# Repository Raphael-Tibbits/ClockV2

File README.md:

# ClockV2
Crystal oscilator clock project

This project aims to create a 1s/year accurate clock, this is done with an ovenated crystal oscilator. 

There are two versions of the hardware, one with a discrete XO, which can be trimmed; and the other with a TCXO module that cant be trimmed

The hardware is made to be IEEE1101.3 compliant form factor as a 3U x 160 deep eurocard that occoupies 4HP. Mechanical stuff like a front panel is still to come.

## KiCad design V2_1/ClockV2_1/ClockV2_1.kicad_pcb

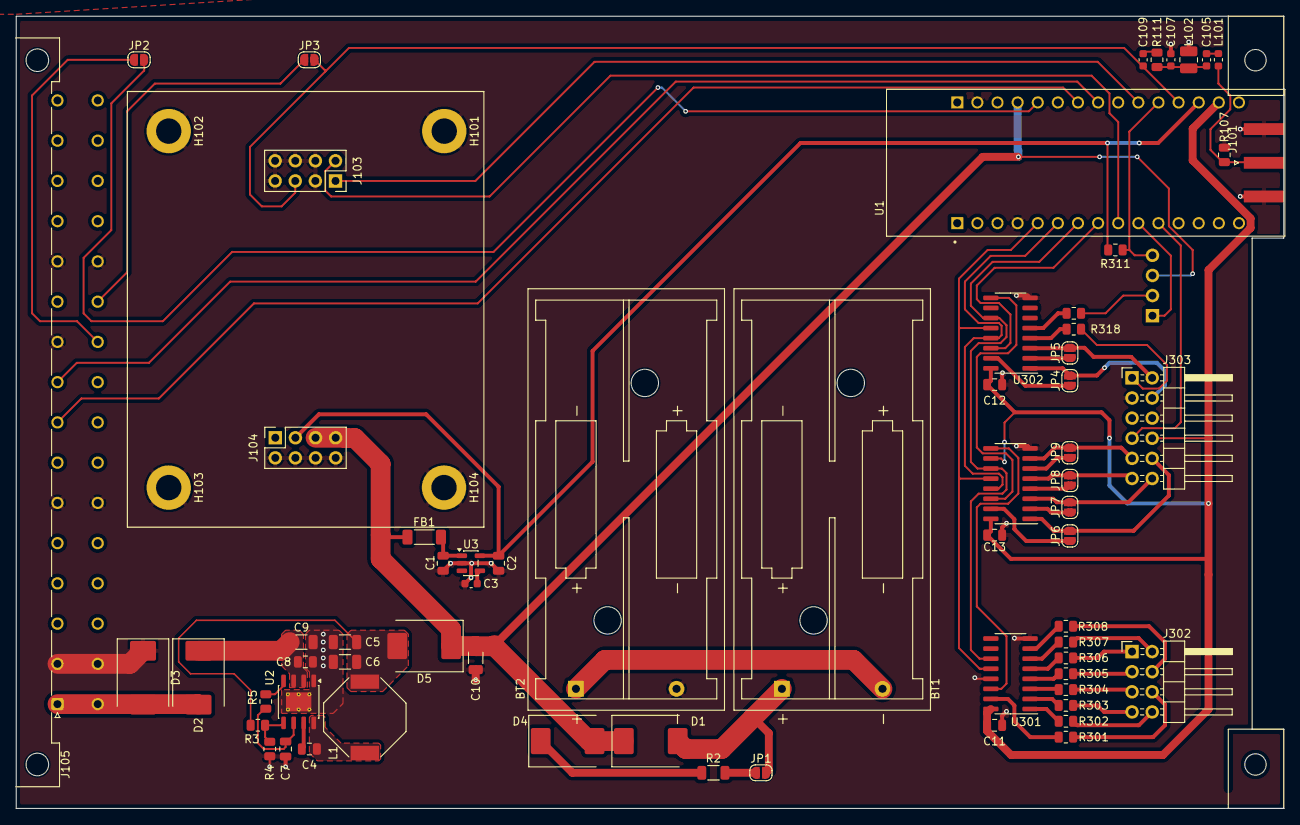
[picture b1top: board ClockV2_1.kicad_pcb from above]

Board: 2 copper layers, 160.0 x 100.0 mm, 70 parts (1 on the bottom side), 71 nets.

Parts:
BT1, BT2: 2.4V 2s NiMH; BatteryHolder_Keystone_2468_2xAAA
C1, C7, C11, C12, C13: 1u; C_0805_2012Metric
C2: 2.2u; C_0805_2012Metric
C3: 10n; C_0603_1608Metric
C4: 100n; C_0805_2012Metric
C5, C6, C10: 22u; C_1206_3216Metric
C8: 220n; C_0805_2012Metric
C9: 10u; C_1206_3216Metric
C105: 15p; C_0603_1608Metric
C107, C109: 150p; C_0603_1608Metric
D1, D2, D4, D5: B320; D_SMC
D3: 1.5SMCxxCA; D_SMC
FB1: FerriteBead; L_1806_4516Metric
H101, H102, H103, H104: MountingHole_Pad; MountingHole_3.2mm_M3_DIN965_Pad
J101: Conn_Coaxial; SMA_Amphenol_132289_EdgeMount
J103, J104: Conn_02x04_Odd_Even; PinSocket_2x04_P2.54mm_Vertical
J105: DIN41612_02x16_AC_EvenPins; DIN41612_C_2x16_Male_Horizontal_THT
J302: Conn_02x04_Odd_Even; PinHeader_2x04_P2.54mm_Horizontal
J303: Conn_02x06_Odd_Even; PinHeader_2x06_P2.54mm_Horizontal
JP1, JP2, JP3, JP4, JP5, JP6, JP7, JP8, JP9: SolderJumper_2_Open; SolderJumper-2_P1.3mm_Open_RoundedPad1.0x1.5mm
L1: 1.5u; L_Bourns-SRU1028_10.0x10.0mm
L101: 8.4u 2%; L_0603_1608Metric
L102: 620n 2%; L_1008_2520Metric
R2: 22R; R_1206_3216Metric
R3: 107k; R_0805_2012Metric
R4: 24.9k; R_0805_2012Metric
R5: 100k; R_0805_2012Metric
R107, R311: 1k; R_0805_2012Metric
R111: 330R; R_0805_2012Metric
R301, R302, R303, R304, R305, R306, R307, R308, R310, R318: 150; R_0805_2012Metric
U1: NUCLEO-L432KC; MODULE_NUCLEO-L432KC
U2: LMR33630CDDA; HTSOP-8-1EP_3.9x4.9mm_P1.27mm_EP2.4x3.2mm_ThermalVias
U3: LP2985-33DBVR; SOT-23-5
U301, U302, U303: 74HC595; SOIC-16_3.9x9.9mm_P1.27mm
j304: Conn_01x04; PinHeader_1x04_P2.54mm_Horizontal

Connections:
+3.3V: C11.1, C12.1, C13.1, J303.8, U1.CN4_14 (+3V3), U301.10 (~SRCLR), U301.16 (VCC), U302.10 (~SRCLR), U302.16 (VCC), U303.10 (~SRCLR), U303.16 (VCC)
+3.3VA: C2.1, J104.3, R311.1, U1.CN4_13 (AREF), U3.5 (VOUT)
+5V: C10.1, D1.1 (K), D4.2 (A), D5.1 (K), FB1.1, J104.5, J104.7, U1.CN4_4 (+5V), j304.3
+12P: D2.2 (A), D3.2 (A2), J105.a2, J105.c2
+12V: C8.2, C9.1, D2.1 (K), U2.2 (VIN), U2.3 (EN)
/1Hz: JP2.2 (B), U1.CN4_5 (PA2)
/16MHz sine: J101.1 (In), L101.2, R107.1
/Display driver and io/A1: J303.4, JP4.2 (B), U302.1 (QB)
/Display driver and io/A2: J303.2, JP5.2 (B), U302.3 (QD)
/Display driver and io/A5: J303.9, JP9.2 (B), U303.7 (QH)
/Display driver and io/A6: J303.11, JP8.2 (B), U303.5 (QF)
/Display driver and io/A7: J303.12, JP7.2 (B), U303.3 (QD)
/Display driver and io/A8: J303.10, JP6.2 (B), U303.1 (QB)
/Display driver and io/LED2: J303.1, R318.2
/Display driver and io/LED3: R310.1, j304.2
/Display driver and io/a: J302.2, R307.2
/Display driver and io/b: J302.1, R306.2
/Display driver and io/c: J302.5, R304.2
/Display driver and io/d: J302.8, R302.2
/Display driver and io/dp: J302.7, R303.2
/Display driver and io/e: J302.6, R301.2
/Display driver and io/f: J302.4, R308.2
/Display driver and io/g: J302.3, R305.2
/Heater_PWM: J103.2, U1.CN3_9 (PB1)
/OE: U1.CN3_6 (PB0), U302.13 (~OE), U303.13 (~OE)
/Ock: U1.CN3_5 (PA12), U301.12 (RCLK), U302.12 (RCLK), U303.12 (RCLK)
/SDA: U1.CN3_8 (PB6), U302.14 (SER)
/Thermistor: J103.1, U1.CN4_10 (PA3)
/Xtal: C109.1, J103.5, JP3.2 (B), U1.CN4_12 (PA0)
/sck: U1.CN3_7 (PB7), U301.11 (SRCLK), U302.11 (SRCLK), U303.11 (SRCLK)
Button: J303.7, U1.CN3_11 (PC15)
GND: BT2.2 (-), C1.2, C2.2, C3.2, C5.2, C6.2, C7.2, C8.1, C9.2, C10.2, C11.2, C12.2, C13.2, C107.2, D3.1 (A1), H101.1, H102.1, H103.1, H104.1, J101.2 (Ext), J103.3, J103.4, J103.6, J103.7, J103.8, J104.2, J104.4, J104.6, J104.8, J105.a4, J105.a12, J105.a20, J105.a24, J105.c4, J105.c12, J105.c24, J303.3, J303.6, L102.2, R4.2, R107.2, U1.CN3_4 (GND_CN3), U1.CN4_2 (GND_CN4), U2.1 (GND), U2.9 (GND), U3.2 (GND), U301.8 (GND), U301.13 (~OE), U302.8 (GND), U303.8 (GND)
I2C SCL: J105.a16, U1.CN4_7 (PA6)
I2C SDA: J105.a18, U1.CN4_8 (PA5)
LED: U1.CN3_10 (PC14), j304.1
unnamed: BT1.1 (+), D1.2 (A), JP1.2 (B)
unnamed: BT1.2 (-), BT2.1 (+)
unnamed: C105.1, C107.1, L102.1, R111.2
unnamed: C105.2, L101.1
unnamed: C109.2, R111.1
unnamed: D4.1 (K), R2.1
unnamed: C5.1, C6.1, D5.2 (A), L1.2, R3.1
unnamed: J105.c20, JP2.1 (A)
unnamed: J105.c22, JP3.1 (A)
unnamed: JP1.1 (A), R2.2
unnamed: JP4.1 (A), U302.15 (QA)
unnamed: JP5.1 (A), U302.2 (QC)
unnamed: JP6.1 (A), U303.15 (QA)
unnamed: JP7.1 (A), U303.2 (QC)
unnamed: JP8.1 (A), U303.4 (QE)
unnamed: JP9.1 (A), U303.6 (QG)
unnamed: C4.1, U2.7 (BOOT)
unnamed: R3.2, R4.1, U2.5 (FB)
unnamed: R5.2, U2.4 (PG)
unnamed: C4.2, L1.1, U2.8 (SW)
unnamed: C7.1, R5.1, U2.6 (VCC)
unnamed: C3.1, U3.4 (BYP)
unnamed: C1.1, FB1.2, U3.1 (VIN), U3.3 (ON/~OFF)
unnamed: R301.1, U301.15 (QA)
unnamed: R302.1, U301.1 (QB)
unnamed: R303.1, U301.2 (QC)
unnamed: R304.1, U301.3 (QD)
unnamed: R305.1, U301.4 (QE)
unnamed: R306.1, U301.5 (QF)
unnamed: R307.1, U301.6 (QG)
unnamed: R308.1, U301.7 (QH)
unnamed: U301.14 (SER), U303.9 (QH')
unnamed: R318.1, U302.4 (QE)
unnamed: R310.2, U302.5 (QF)
unnamed: U302.9 (QH'), U303.14 (SER)
light_sense: R311.2, U1.CN4_11 (PA1), j304.4

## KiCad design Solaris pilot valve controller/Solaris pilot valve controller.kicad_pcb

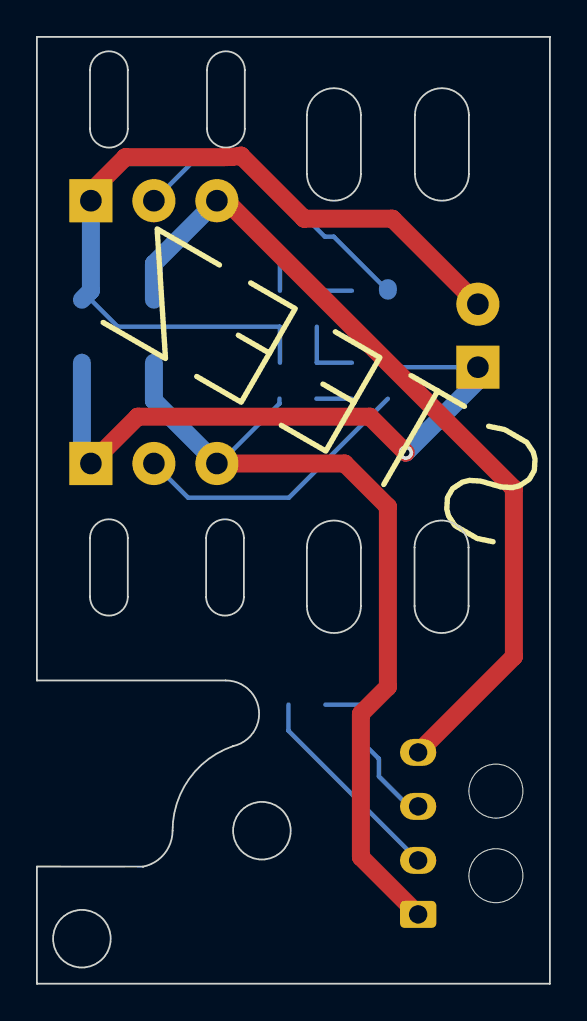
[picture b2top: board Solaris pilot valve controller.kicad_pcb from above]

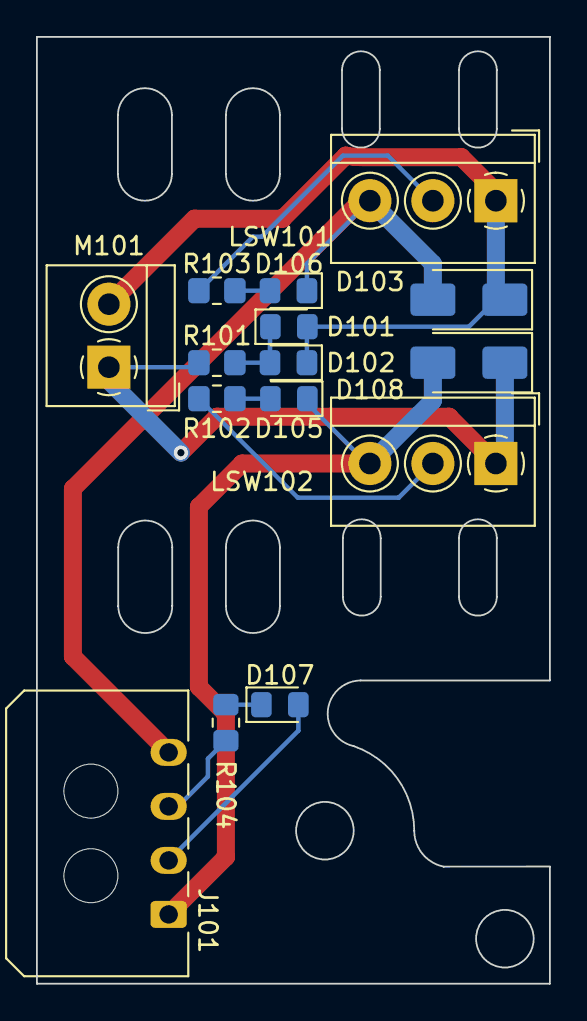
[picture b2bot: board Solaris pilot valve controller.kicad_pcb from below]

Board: 2 copper layers, 28.5 x 52.6 mm, 15 parts (15 on the bottom side), 12 nets.

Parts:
D101, D102, D105, D106, D107: LED; LED_0805_2012Metric_Pad1.15x1.40mm_HandSolder
D103, D108: M7; D_SMA
J101: 436500401; Molex_Micro-Fit_3.0_43650-0400_1x04_P3.00mm_Horizontal
LSW101, LSW102: SW_SPDT; TerminalBlock_4Ucon_1x03_P3.50mm_Horizontal
M101: Motor_DC_ALT; TerminalBlock_4Ucon_1x02_P3.50mm_Horizontal
R101, R102, R103, R104: 470R; R_0805_2012Metric_Pad1.20x1.40mm_HandSolder

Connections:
unnamed: D101.2 (A), D102.1 (K), D103.1 (K), LSW101.1 (COM), M101.2 (-)
unnamed: D101.1 (K), D102.2 (A), R101.1
unnamed: D103.2 (A), D106.1 (K), J101.4, LSW101.3 (NC)
unnamed: D105.2 (A), R102.1
unnamed: D105.1 (K), D108.2 (A), J101.1, LSW102.3 (NC)
unnamed: D106.2 (A), R103.1
unnamed: D107.2 (A), J101.2
unnamed: D107.1 (K), R104.2
unnamed: D108.1 (K), LSW102.1 (COM), M101.1 (+), R101.2
unnamed: J101.3, R104.1
unnamed: LSW101.2 (NO), R103.2
unnamed: LSW102.2 (NO), R102.2

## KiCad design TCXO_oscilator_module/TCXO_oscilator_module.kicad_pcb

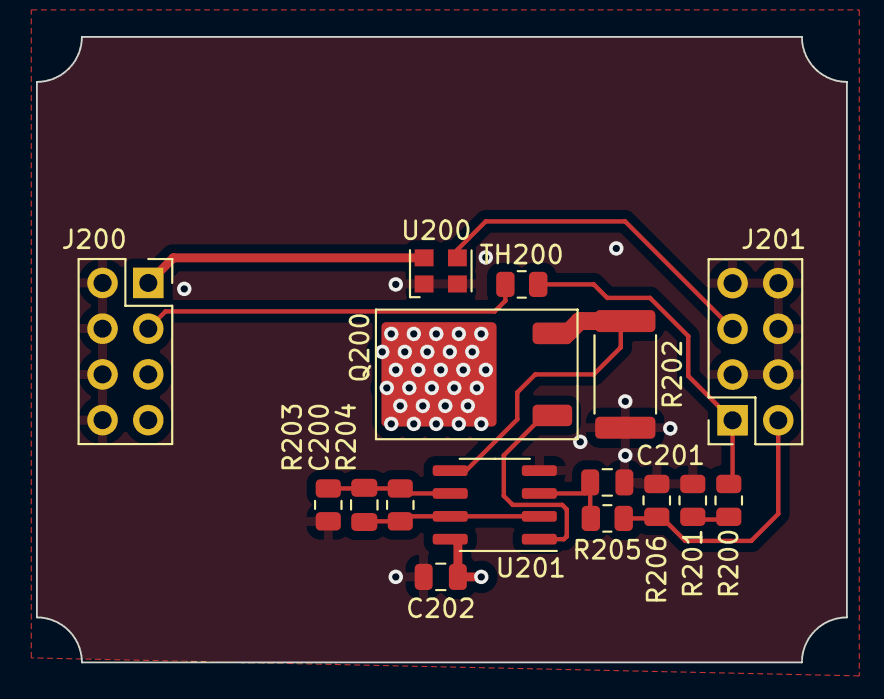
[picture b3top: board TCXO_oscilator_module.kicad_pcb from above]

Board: 4 copper layers, 45.0 x 34.8 mm, 16 parts (0 on the bottom side), 13 nets.

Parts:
C200, C201, C202: 1u; C_0805_2012Metric
J200, J201: Conn_02x04_Odd_Even; PinSocket_2x04_P2.54mm_Vertical
Q200: IRLR024N; TO-252-2
R200, R201, R203: 1k; R_0805_2012Metric
R202: 0.02R; R_2512_6332Metric
R204, R205, R206: 47k; R_0805_2012Metric
TH200: Thermistor_NTC; R_0805_2012Metric
U200: KC2520Z; Oscillator_SMD_Kyocera_KC2520Z-4Pin_2.5x2.0mm
U201: LMV358; SOIC-8_3.9x4.9mm_P1.27mm

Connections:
+2V5: J200.1, U200.4 (VCC)
+3.3VA: J200.3, TH200.1
+5V: C202.1, J200.5, J200.7, Q200.2 (D), U201.8 (V+)
/Heater_PWM: J201.2, R205.2, R206.2
/Thermistor: J201.1, R200.1, TH200.2
/XTAL1: J201.5, U200.3 (CLK)
GND: C201.2, C202.2, J200.2, J200.4, J200.6, J200.8, J201.3, J201.4, J201.6, J201.7, J201.8, R201.2, R202.2, R203.2, R206.1, U200.1 (INH), U200.2 (GND), U201.4 (V-)
unnamed: Q200.1 (G), U201.1
unnamed: Q200.3 (S), R202.1, U201.5 (+)
unnamed: R200.2, R201.1
unnamed: C201.1, R205.1, U201.3 (+)
unnamed: C200.2, R204.2, U201.2 (-), U201.7
unnamed: C200.1, R203.1, R204.1, U201.6 (-)

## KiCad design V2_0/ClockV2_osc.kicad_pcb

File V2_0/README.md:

# ClockV2
Crystal oscilator clock project

This project aims to create a 1s/year accurate clock, this is done with an ovenated crystal oscilator. 

There are two versions of the hardware, one with a discrete XO, which can be trimmed; and the other with a TCXO module that cant be trimmed

The hardware is made to be IEEE1101.3 compliant form factor as a 3U x 160 deep eurocard that occoupies 4HP. Mechanical stuff like a front panel is in progress

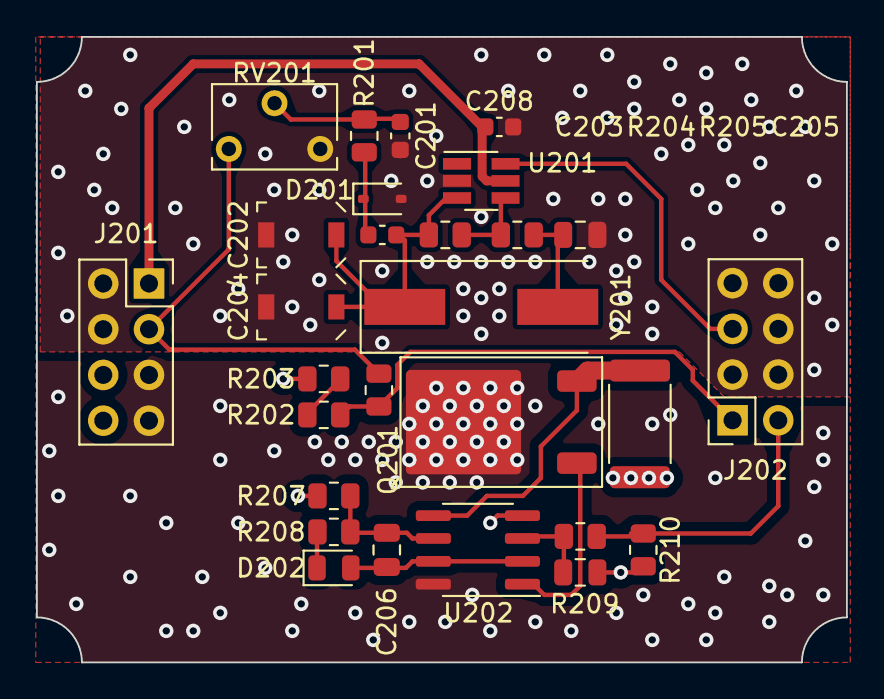
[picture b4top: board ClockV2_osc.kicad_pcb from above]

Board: 4 copper layers, 45.0 x 34.8 mm, 28 parts (0 on the bottom side), 19 nets.

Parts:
C201, C208: 10n; C_0603_1608Metric
C202: 0.1-2p; C_Trimmer_Voltronics_JZ
C203: 150p; C_0603_1608Metric
C204: 3-30p; C_Trimmer_Voltronics_JZ
C205: 22p C0G; C_0805_2012Metric
C206, C207: 1u; C_0805_2012Metric
D201: 1N4148WS; D_SOD-323
D202: LED; LED_0805_2012Metric
J201, J202: Conn_02x04_Odd_Even; PinSocket_2x04_P2.54mm_Vertical
Q201: IRLR024N; TO-252-2
R201, R208, R209, R210: 47k; R_0805_2012Metric
R202, R203, R207: 1k; R_0805_2012Metric
R204: 5M; R_0805_2012Metric
R205: 470R; R_0805_2012Metric
R206: 0.02R; R_2512_6332Metric
RV201: 10k; Potentiometer_Bourns_3266W_Vertical
TH201: Thermistor_NTC; R_0805_2012Metric
U201: 74LVC1GX04; SOT-23-6_Handsoldering
U202: LMV358; SOIC-8_3.9x4.9mm_P1.27mm
Y201: 16MHz; Crystal_SMD_HC49-SD

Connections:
+2V5: C208.1, J201.1, U201.5 (VCC)
+3.3VA: J201.3, RV201.1, TH201.1
+5V: J201.5, J201.7, Q201.2 (D), U202.8 (V+)
/16MHz clk: J202.5, U201.6 (Y)
/Heat: J202.2, R209.2, R210.2
/Temp: J202.1, R202.1, TH201.2
GND: C201.2, C202.2, C204.2, C205.2, C207.2, C208.2, D201.2 (A), J201.2, J201.4, J201.6, J201.8, J202.3, J202.4, J202.6, J202.7, J202.8, R203.2, R206.2, R207.2, R210.1, RV201.3, U201.2 (GND), U202.4 (V-)
unnamed: C201.1, R201.1, RV201.2
unnamed: C205.1, R205.2, Y201.2
unnamed: C203.1, D201.1 (K), R201.2
unnamed: C206.2, D202.2 (A), U202.2 (-), U202.7
unnamed: D202.1 (K), R208.2
unnamed: Q201.1 (G), U202.1
unnamed: Q201.3 (S), R206.1, U202.5 (+)
unnamed: R202.2, R203.1
unnamed: C202.1, C203.2, C204.1, R204.2, U201.3 (X1), Y201.1
unnamed: R204.1, R205.1, U201.4 (X2)
unnamed: C207.1, R209.1, U202.3 (+)
unnamed: C206.1, R207.1, R208.1, U202.6 (-)

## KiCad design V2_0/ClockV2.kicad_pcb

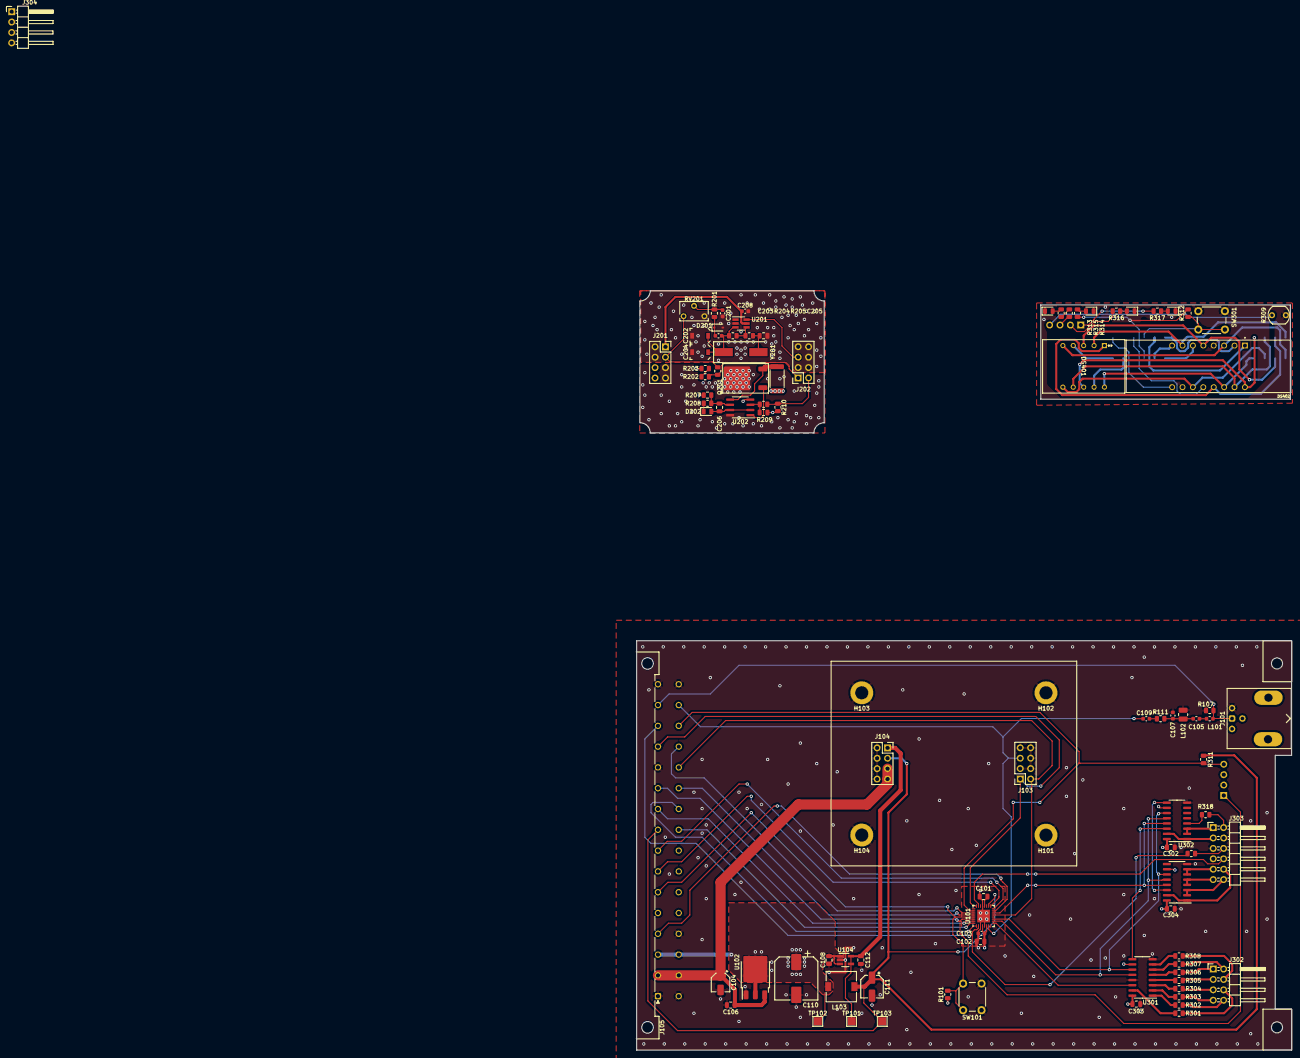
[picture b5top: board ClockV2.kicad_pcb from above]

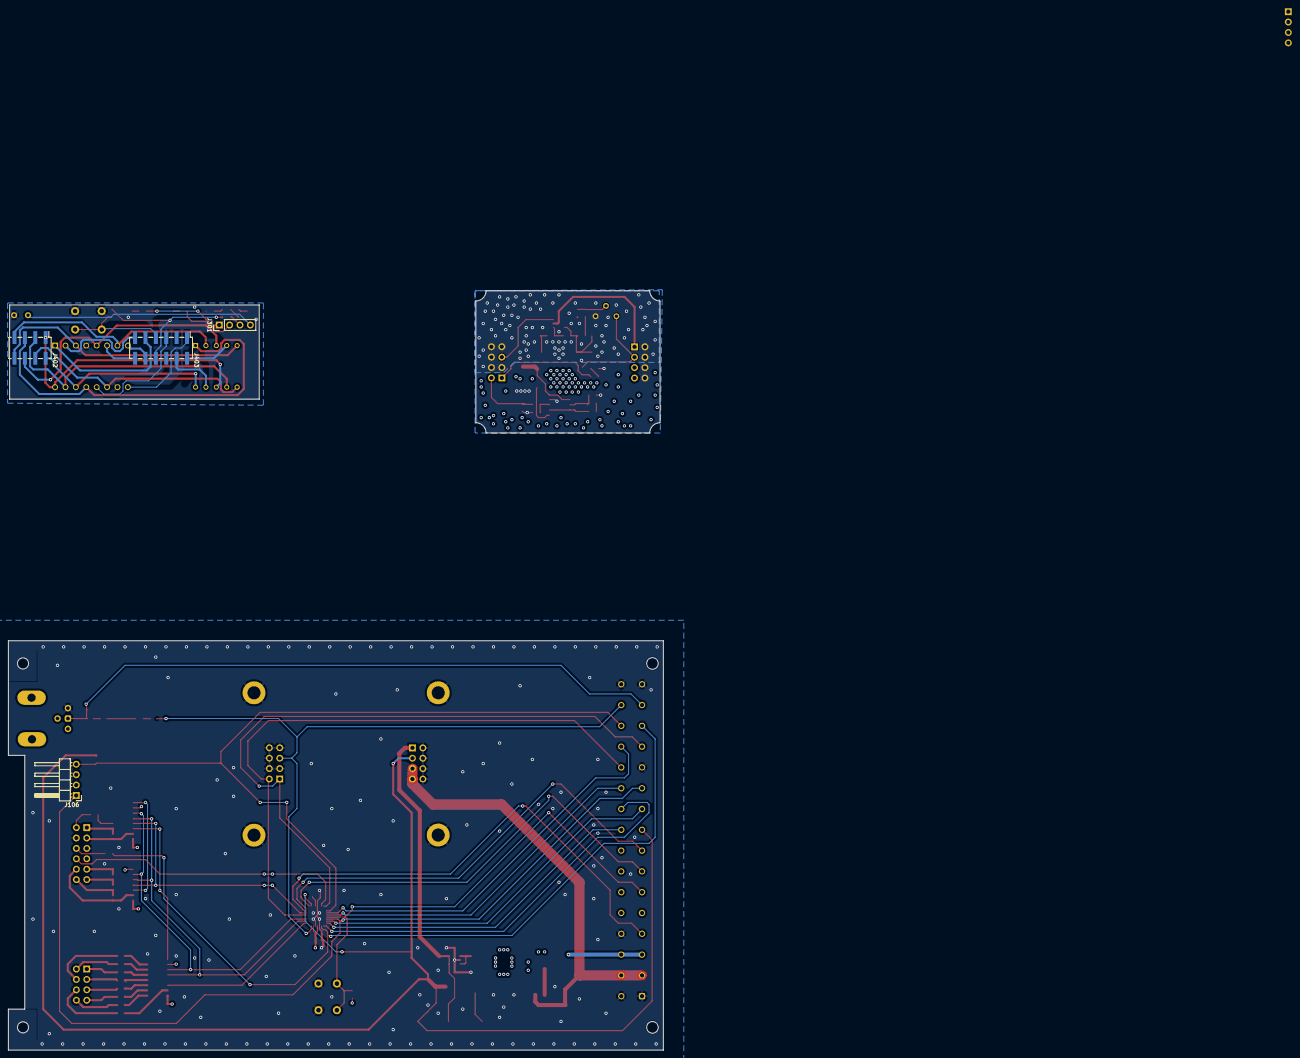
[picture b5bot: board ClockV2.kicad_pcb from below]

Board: 4 copper layers, 160.0 x 185.5 mm, 99 parts (4 on the bottom side), 74 nets.

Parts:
C101, C106, C108, C206, C207, C302, C303, C304: 1u; C_0805_2012Metric
C102: 100n; C_0805_2012Metric
C103, C201, C208: 10n; C_0603_1608Metric
C104: 4.7u; CP_Elec_4x3
C105: 15p; C_0603_1608Metric
C107, C109, C203: 150p; C_0603_1608Metric
C110: 220u; CP_Elec_10x10
C111: 47u; CP_Elec_5x3.9
C112: 2.2u; C_0805_2012Metric
C202: 0.1-2p; C_Trimmer_Voltronics_JZ
C204: 3-30p; C_Trimmer_Voltronics_JZ
C205: 22p C0G; C_0805_2012Metric
D201: 1N4148WS; D_SOD-323
D202: LED; LED_0805_2012Metric
D301, D302, D303: RED; LED_0805_2012Metric
D304: GRN; LED_0805_2012Metric
DS401: LTD-4608JR; LTD-4608JR_LTO
DS402: TDCR1060M; DISPLAY_TDCR1060M
H101, H102, H103, H104: MountingHole_Pad; MountingHole_3.2mm_M3_DIN965_Pad
J101: Conn_Coaxial; BNC_Amphenol_031-6575_Horizontal
J103, J104, J201, J202: Conn_02x04_Odd_Even; PinSocket_2x04_P2.54mm_Vertical
J105: DIN41612_02x16_AC_EvenPins; DIN41612_C_2x16_Male_Horizontal_THT
J106, J304: Conn_01x04; PinHeader_1x04_P2.54mm_Horizontal
J301: Conn_01x04; PinHeader_1x04_P2.54mm_Vertical
J302: Conn_02x04_Odd_Even; PinHeader_2x04_P2.54mm_Horizontal
J303: Conn_02x06_Odd_Even; PinHeader_2x06_P2.54mm_Horizontal
J402: Conn_02x04_Odd_Even; PinHeader_2x04_P2.54mm_Vertical_SMD
J403: Conn_02x06_Odd_Even; PinHeader_2x06_P2.54mm_Vertical_SMD
L101: 8.4u 2%; L_0603_1608Metric
L102: 620n 2%; L_1008_2520Metric
L103: 1m; L_7.3x7.3_H3.5
Q201: IRLR024N; TO-252-2
R101, R201, R208, R209, R210: 47k; R_0805_2012Metric
R107, R202, R203, R207, R311, R312: 1k; R_0805_2012Metric
R111, R313, R314, R315: 330R; R_0805_2012Metric
R204: 5M; R_0805_2012Metric
R205: 470R; R_0805_2012Metric
R206: 0.02R; R_2512_6332Metric
R301, R302, R303, R304, R305, R306, R307, R308, R310, R316, R317, R318: 150; R_0805_2012Metric
R309: LDR03; R_LDR_5.1x4.3mm_P3.4mm_Vertical
RV201: 10k; Potentiometer_Bourns_3266W_Vertical
SW101, SW301: SW_Push; SW_PUSH_6mm_H4.3mm
TH201: Thermistor_NTC; R_0805_2012Metric
TP101, TP102, TP103: TestPoint; TestPoint_Pad_2.0x2.0mm
U101: ATmega328P-M; QFN-32-1EP_5x5mm_P0.5mm_EP3.1x3.1mm
U102: LM1117DT-3.3; TO-252-3_TabPin2
U104: ADP7142ARDZ-2.5; SOT-23-5_HandSoldering
U201: 74LVC1GX04; SOT-23-6_Handsoldering
U202: LMV358; SOIC-8_3.9x4.9mm_P1.27mm
U301, U302, U303: 74HC595; SOIC-16_3.9x9.9mm_P1.27mm
Y201: 16MHz; Crystal_SMD_HC49-SD

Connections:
+2V5: C112.1, C208.1, J104.1, J106.2, J201.1, J301.2, J304.2, R316.2, TP101.1, U104.4 (SENSE/ADJ), U104.5 (VOUT), U201.5 (VCC)
+3.3V: C102.1, C103.1, C108.1, C110.1, C302.1, C303.1, C304.1, J105.a6, J105.c6, J303.7, J403.8, L103.1, R101.1, R312.1, R314.1, TP102.1, U101.4 (VCC), U101.6 (VCC), U102.2 (VO), U104.1 (VIN), U104.3 (EN), U301.10 (~SRCLR), U301.16 (VCC), U302.10 (~SRCLR), U302.16 (VCC), U303.10 (~SRCLR), U303.16 (VCC)
+3.3VA: C111.1, J104.3, J105.a18, J201.3, L103.2, R311.1, RV201.1, TH201.1, TP103.1, U101.18 (AVCC)
+5V: C104.1, C106.1, J104.5, J104.7, J105.a4, J105.c4, J106.3, J201.5, J201.7, J301.3, J304.3, Q201.2 (D), R315.1, U102.3 (VI), U202.8 (V+)
/1Hz: J105.a28, R310.2, U101.2 (PD4)
/7 seg Display/1PPS: DS402.12, J303.6, J403.5, R310.1
/7 seg Display/A1: DS401.9, J303.3, J403.4, U302.1 (QB), U302.15 (QA)
/7 seg Display/A2: DS401.4, J303.1, J403.2, U302.2 (QC), U302.3 (QD)
/7 seg Display/A5: DS402.1, J303.10, J403.9, U303.1 (QB), U303.15 (QA)
/7 seg Display/A6: DS402.2, J303.12, J403.11, U303.2 (QC), U303.3 (QD)
/7 seg Display/A7: DS402.6, J303.11, J403.12, U303.4 (QE), U303.5 (QF)
/7 seg Display/A8: DS402.8, J303.9, J403.10, U303.6 (QG), U303.7 (QH)
/7 seg Display/LED2: DS402.9, J303.2, J403.1, R318.2
/7 seg Display/ORClk: U101.10 (PD6), U301.12 (RCLK), U302.12 (RCLK), U303.12 (RCLK)
/7 seg Display/OutEn: U101.14 (PB2), U302.13 (~OE), U303.13 (~OE)
/7 seg Display/Sclk: U101.11 (PD7), U301.11 (SRCLK), U302.11 (SRCLK), U303.11 (SRCLK)
/7 seg Display/SerData: U101.9 (PD5), U301.14 (SER)
/7 seg Display/a: DS401.10, DS402.14, J302.2, J402.2, R307.2
/7 seg Display/b: DS401.8, DS402.16, J302.1, J402.1, R306.2
/7 seg Display/c: DS401.1, DS402.13, J302.5, J402.5, R304.2
/7 seg Display/d: DS401.5, DS402.3, J302.8, J402.8, R302.2
/7 seg Display/dp: DS401.2, DS402.7, J302.7, J402.7, R303.2
/7 seg Display/e: DS401.3, DS402.5, J302.6, J402.6, R301.2
/7 seg Display/f: DS401.6, DS402.11, J302.4, J402.4, R308.2
/7 seg Display/g: DS401.7, DS402.15, J302.3, J402.3, R305.2
/16MHz clk: C109.1, J103.5, J105.c30, J202.5, U101.7 (XTAL1/PB6), U201.6 (Y)
/16MHz sine: J101.1 (In), J105.a30, L101.2, R107.1
/AIO0: J105.c22, U101.28 (PC5)
/AIO1: J105.c26, U101.27 (PC4)
/DIO0: J105.a20, U101.31 (PD1)
/DIO1: J105.c18, U101.32 (PD2)
/DIO2: J105.c20, U101.1 (PD3)
/Heat: J103.2, J105.c24, J202.2, R209.2, R210.2, U101.13 (PB1)
/Temp: J103.1, J105.a26, J202.1, R202.1, TH201.2, U101.24 (PC1)
/miso: J105.a16, U101.16 (PB4)
/mosi: J105.a8, U101.15 (PB3)
/rst: J105.a12, R101.2, SW101.1, U101.29 (~RESET/PC6)
/sck: J105.a14, U101.17 (PB5)
Button: J303.8, J403.7, R312.2, SW301.1, U101.23 (PC0)
GND: C101.2, C102.2, C103.2, C104.2, C106.2, C107.2, C108.2, C110.2, C111.2, C112.2, C201.2, C202.2, C204.2, C205.2, C207.2, C208.2, C302.2, C303.2, C304.2, D201.2 (A), D301.1 (K), D302.1 (K), D303.1 (K), D304.1 (K), DS402.4, DS402.10, H101.1, H102.1, H103.1, H104.1, J101.2 (Ext), J103.3, J103.4, J103.6, J103.7, J103.8, J104.2, J104.4, J104.6, J104.8, J105.a2, J105.a24, J105.a32, J105.c2, J105.c8, J105.c32, J201.2, J201.4, J201.6, J201.8, J202.3, J202.4, J202.6, J202.7, J202.8, J303.4, J303.5, J403.3, J403.6, L102.2, R107.2, R203.2, R206.2, R207.2, R210.1, R309.2, RV201.3, SW101.2, SW301.2, U101.3 (GND), U101.5 (GND), U101.21 (GND), U101.33 (GND), U102.1 (GND), U104.2 (GND), U201.2 (GND), U202.4 (V-), U301.8 (GND), U301.13 (~OE), U302.8 (GND), U303.8 (GND)
LED: J105.a22, J106.1, J301.1, J304.1, R317.2, U101.30 (PD0)
unnamed: C105.1, C107.1, L102.1, R111.2
unnamed: C105.2, L101.1
unnamed: C109.2, R111.1
unnamed: C201.1, R201.1, RV201.2
unnamed: C205.1, R205.2, Y201.2
unnamed: C203.1, D201.1 (K), R201.2
unnamed: C206.2, D202.2 (A), U202.2 (-), U202.7
unnamed: D202.1 (K), R208.2
unnamed: D301.2 (A), R313.2
unnamed: D302.2 (A), R314.2
unnamed: D303.2 (A), R316.1
unnamed: D304.2 (A), R317.1
unnamed: Q201.1 (G), U202.1
unnamed: Q201.3 (S), R206.1, U202.5 (+)
unnamed: R202.2, R203.1
unnamed: R313.1, R315.2
unnamed: C101.1, U101.20 (AREF)
unnamed: C202.1, C203.2, C204.1, R204.2, U201.3 (X1), Y201.1
unnamed: R204.1, R205.1, U201.4 (X2)
unnamed: C207.1, R209.1, U202.3 (+)
unnamed: C206.1, R207.1, R208.1, U202.6 (-)
unnamed: R301.1, U301.15 (QA)
unnamed: R302.1, U301.1 (QB)
unnamed: R303.1, U301.2 (QC)
unnamed: R304.1, U301.3 (QD)
unnamed: R305.1, U301.4 (QE)
unnamed: R306.1, U301.5 (QF)
unnamed: R307.1, U301.6 (QG)
unnamed: U301.9 (QH'), U302.14 (SER)
unnamed: R308.1, U301.7 (QH)
unnamed: R318.1, U302.4 (QE)
unnamed: U302.9 (QH'), U303.14 (SER)
light_sense: J105.c28, J106.4, J301.4, J304.4, R309.1, R311.2, U101.26 (PC3)

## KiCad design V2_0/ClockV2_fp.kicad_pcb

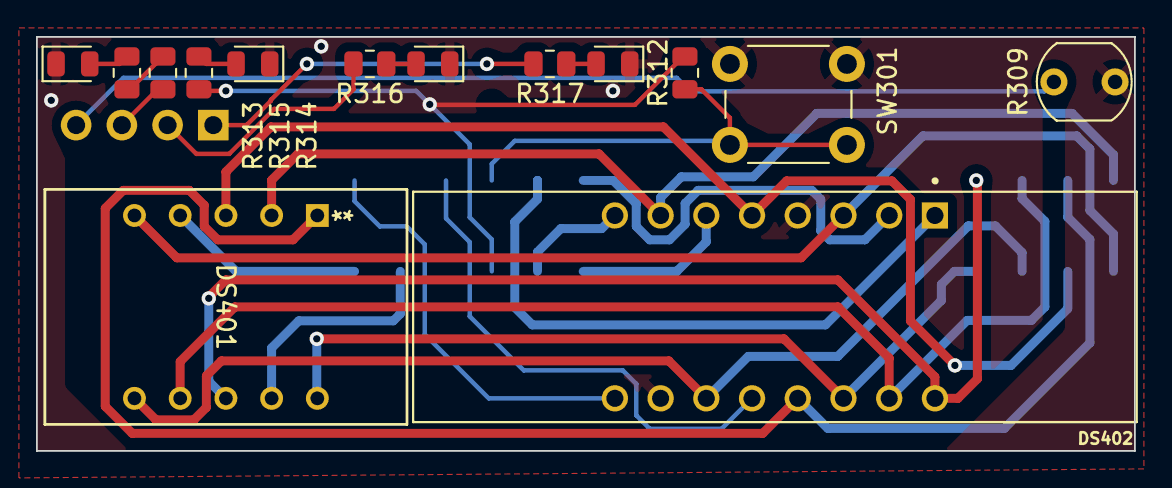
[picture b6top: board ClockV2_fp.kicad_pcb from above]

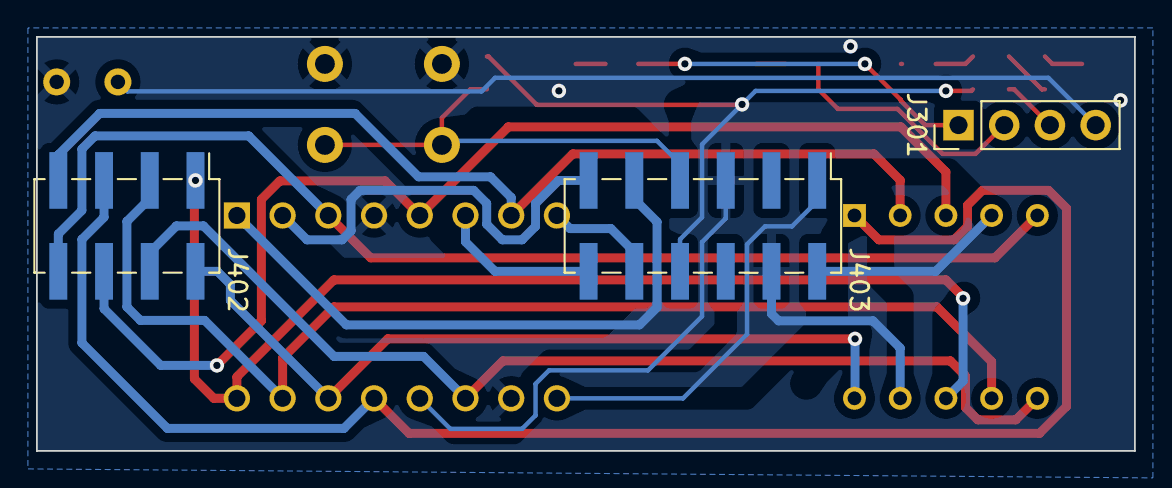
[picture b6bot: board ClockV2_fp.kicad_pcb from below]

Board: 4 copper layers, 61.0 x 23.0 mm, 17 parts (3 on the bottom side), 28 nets.

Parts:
D301, D302, D303: RED; LED_0805_2012Metric
D304: GRN; LED_0805_2012Metric
DS401: LTD-4608JR; LTD-4608JR_LTO
DS402: TDCR1060M; DISPLAY_TDCR1060M
J301: Conn_01x04; PinHeader_1x04_P2.54mm_Vertical
J402: Conn_02x04_Odd_Even; PinHeader_2x04_P2.54mm_Vertical_SMD
J403: Conn_02x06_Odd_Even; PinHeader_2x06_P2.54mm_Vertical_SMD
R309: LDR03; R_LDR_5.1x4.3mm_P3.4mm_Vertical
R312: 1k; R_0805_2012Metric
R313, R314, R315: 330R; R_0805_2012Metric
R316, R317: 150; R_0805_2012Metric
SW301: SW_Push; SW_PUSH_6mm_H4.3mm

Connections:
+2V5: J301.2, R316.2
+3.3V: J403.8, R312.1, R314.1
+5V: J301.3, R315.1
/7 seg Display/1PPS: DS402.12, J403.5
/7 seg Display/A1: DS401.9, J403.4
/7 seg Display/A2: DS401.4, J403.2
/7 seg Display/A5: DS402.1, J403.9
/7 seg Display/A6: DS402.2, J403.11
/7 seg Display/A7: DS402.6, J403.12
/7 seg Display/A8: DS402.8, J403.10
/7 seg Display/LED2: DS402.9, J403.1
/7 seg Display/a: DS401.10, DS402.14, J402.2
/7 seg Display/b: DS401.8, DS402.16, J402.1
/7 seg Display/c: DS401.1, DS402.13, J402.5
/7 seg Display/d: DS401.5, DS402.3, J402.8
/7 seg Display/dp: DS401.2, DS402.7, J402.7
/7 seg Display/e: DS401.3, DS402.5, J402.6
/7 seg Display/f: DS401.6, DS402.11, J402.4
/7 seg Display/g: DS401.7, DS402.15, J402.3
Button: J403.7, R312.2, SW301.1
GND: D301.1 (K), D302.1 (K), D303.1 (K), D304.1 (K), DS402.4, DS402.10, J403.3, J403.6, R309.2, SW301.2
LED: J301.1, R317.2
unnamed: D301.2 (A), R313.2
unnamed: D302.2 (A), R314.2
unnamed: D303.2 (A), R316.1
unnamed: D304.2 (A), R317.1
unnamed: R313.1, R315.2
light_sense: J301.4, R309.1

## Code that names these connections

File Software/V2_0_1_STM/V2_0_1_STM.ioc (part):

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Mcu.Name=STM32L432K(B-C)Ux
Mcu.Package=UFQFPN32
Mcu.UserName=STM32L432KCUx
PA0.GPIOParameters=GPIO_Label
PA0.GPIO_Label=HSE_16MHZ
PA0.Mode=HSE-External-Clock-Source-for-LittleOrca
PA0.Signal=RCC_CK_IN
PA1.GPIOParameters=GPIO_Label
PA1.GPIO_Label=LDR_sense
PA1.Signal=SharedAnalog_PA1
PA10.Mode=I2C
PA10.Signal=I2C1_SDA
PA2.Mode=Asynchronous
PA2.Signal=USART2_TX
PA3.Mode=Asynchronous
PA3.Signal=USART2_RX
PA4.GPIOParameters=GPIO_Label
PA4.GPIO_Label=Therm_sense
PA4.Signal=SharedAnalog_PA4
PA5.GPIOParameters=GPIO_Label
PA5.GPIO_Label=Display_SCK
PA5.Mode=TX_Only_Simplex_Unidirect_Master
PA5.Signal=SPI1_SCK
PA6.GPIOParameters=GPIO_Label
PA6.GPIO_Label=Display_RCK
PA6.Signal=GPIO_Output
PA7.GPIOParameters=GPIO_Label
PA7.GPIO_Label=Display_MOSI
PA7.Mode=TX_Only_Simplex_Unidirect_Master
PA7.Signal=SPI1_MOSI
PA9.Mode=I2C
PA9.Signal=I2C1_SCL
PB0.GPIOParameters=GPIO_Label
PB0.GPIO_Label=Display_PWM
PB0.Mode=PWM Generation2 CH2N
PB0.Signal=TIM1_CH2N
PB1.GPIOParameters=GPIO_Label
PB1.GPIO_Label=Heater_PWM
PB1.Mode=PWM Generation3 CH3N
PB1.Signal=TIM1_CH3N
PB3\ (JTDO-TRACESWO).Signal=GPIO_Output
RCC.HSE_VALUE=16000000
RCC.SYSCLKFreq_VALUE=64000000
RCC.SYSCLKSource=RCC_SYSCLKSOURCE_PLLCLK
board=custom

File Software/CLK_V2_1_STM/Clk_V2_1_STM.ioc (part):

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Mcu.Name=STM32L432K(B-C)Ux
Mcu.Package=UFQFPN32
Mcu.UserName=STM32L432KCUx
PA0.Mode=HSE-External-Clock-Source-for-LittleOrca
PA0.Signal=RCC_CK_IN
PA1.GPIOParameters=GPIO_Label
PA1.GPIO_Label=Light_sensor
PA1.Signal=ADCx_IN6
PA10.Mode=I2C
PA10.Signal=I2C1_SDA
PA11.GPIOParameters=GPIO_Label
PA11.GPIO_Label=DISP_OE
PA11.Signal=S_TIM1_CH4
PA12.GPIOParameters=GPIO_Label
PA12.GPIO_Label=LED_Front
PA12.Signal=GPIO_Output
PA15\ (JTDI).Mode=Asynchronous
PA15\ (JTDI).Signal=USART2_RX
PA2.Mode=Asynchronous
PA2.Signal=USART2_TX
PA3.GPIOParameters=GPIO_Label
PA3.GPIO_Label=Temp_sensor
PA3.Signal=ADCx_IN8
PA9.Mode=I2C
PA9.Signal=I2C1_SCL
PB1.GPIOParameters=GPIO_Label
PB1.GPIO_Label=Heater
PB1.Mode=PWM Generation3 CH3N
PB1.Signal=TIM1_CH3N
PB3\ (JTDO-TRACESWO).GPIOParameters=GPIO_Label
PB3\ (JTDO-TRACESWO).GPIO_Label=DISP_SCLK
PB3\ (JTDO-TRACESWO).Mode=TX_Only_Simplex_Unidirect_Master
PB3\ (JTDO-TRACESWO).Signal=SPI3_SCK
PB4\ (NJTRST).GPIOParameters=GPIO_Label
PB4\ (NJTRST).GPIO_Label=DISP_ORCLK
PB4\ (NJTRST).Signal=GPIO_Output
PB5.GPIOParameters=GPIO_Label
PB5.GPIO_Label=DISP_SDAT
PB5.Mode=TX_Only_Simplex_Unidirect_Master
PB5.Signal=SPI3_MOSI
RCC.HSE_VALUE=16000000
RCC.SYSCLKFreq_VALUE=64000000
RCC.SYSCLKSource=RCC_SYSCLKSOURCE_PLLCLK
board=custom

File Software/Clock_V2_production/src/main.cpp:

#include <avr/io.h>
#include <clock_peripherals.h>
#include <avr/interrupt.h>
#include <avr/wdt.h>

#include "controller.hpp"
// #include "time.hpp"


#define MAX_TEMP 7000 // max temperature in hundredths of a degree Celsius (60.00C)


volatile uint64_t miliseconds;

volatile uint8_t flag = 0;



Heater_controller Crystal_Oven(1, 0, 6000);


ISR(TIMER0_COMPA_vect){
  // Timer0 interrupt service routine
  // This will be called every 1ms
  miliseconds++;
  flag = 1;
  // uart_send_number(miliseconds);
}

int main()
{

  // setup clock to use external 16MHz oscilatior
  CLKPR = (1 << CLKPCE); // enable change of the clock prescaler
  CLKPR = 0; // set prescaler to 1 (16MHz)

  // Disable interrupts while changing WDT
  cli();

  // Clear WDRF in MCUSR
  MCUSR &= ~(1 << WDRF);

  // Start timed sequence to disable WDT
  wdt_reset();                         // Reset WDT
  WDTCSR |= (1 << WDCE) | (1 << WDE);  // Enable change
  WDTCSR = 0x00;                       // Disable WDT


  // setup timer tick
  timer0_init();

  // setup PWM on Timer 1
  PWM_init();
  set_PWM_period(1024); // set period to 601
  set_PWMA_duty_cycle(0); // start with 0% duty cycle
  set_PWMB_duty_cycle(1024); // start with 0% duty cycle
  // setup ADC
  adc_init();

  sei(); // enable global interrupts

  // setup uart
  UBRR0 = 8; // Set baud rate to 112500 for 16MHz clock
  UCSR0C = (1 << UCSZ01) | (1 << UCSZ00); // Set frame format: 8 data bits, 1 stop bit, no parity
  UCSR0B = (1 << TXEN0) | (1 << RXEN0); // Enable transmitter and receiver

  
  DDRD |= (1 << LED1_PIN) | (1 << DIO2); // Set LED1_PIN and DIO2 as output

  uart_send_string("hello");
  PORTD |= (1 << DIO2);
  _NOP();
  _NOP();
  _NOP();
  _NOP();
  PORTD &= ~(1 << DIO2);

  
  DDRD |= (1 << SEG_SER_PIN) | (1 << SEG_SCLK_PIN) | (1 << SEG_RCLK_PIN); // Set shift register pins as outputs
  DDRC &= ~((1 << BUTTON_PIN) | (1 << Thermistor_Pin) | (1 << LDR_Pin)); // Set button and sensor pins as inputs
  DDRB |= (1 << Heat_Pin); // Set heating element control pin as output
  DDRD |= (1 << One_PPS_Pin); // Set 1PPS signal input pin as output


  while (1) {
    // runs constantly
    
    if (!flag) {
        // runs if nothing else to do
        continue; // Skip the rest of the loop if no new millisecond tick
    }
    flag = 0;

    // 10Hz loop
    if (miliseconds % 100 == 0) {
      // Crystal_Oven.update(miliseconds);

      if((miliseconds >5000UL) && (miliseconds < 6000UL)){
        Crystal_Oven.set_heater_power((uint16_t)1000); // set heater to 1W for 1s
      }

      // uart_send_number_as_text(ovenTemp);
      // uart_send_char('T');
      // uart_send_number_as_text(actuation);
      // uart_send_char('A');

    }

    // 10Hz alternate loop
    if ((miliseconds+50) % 100 == 0) {
      uint16_t light = get_ADC_result(LDR_Pin);
      // uart_send_number(light);
    }

    if (miliseconds % 1000 == 0) {
      uart_send_number_as_text(miliseconds/1000);
      uart_send_char('S');
    }

    

    uint8_t testPattern[3] = {0x00, 0x00, 0x00};
    send_bytes_to_shift_regs(testPattern);

    
  }

  return 0;
}

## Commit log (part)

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2025-10-27 removed incorrect repo
    got rid of the old repo that was made incorrectly
2025-10-27 updated avrtos
    created a branch for avrtos with my mukings
2025-10-27 added detail to readme
2025-11-08 created STM project
    created and setup IOC fro STM version V2.1
2025-11-09 more STM
    added display for the working digits, started adding heater control and added timekeeping with RTC
2025-11-29 New Kicad Project for V2.1
    moved the V2 to a new folder and made V2.1 folder for STM32 version
2025-11-29 started layout
2025-12-04 schematics continued
    added power supplies and main sheet
